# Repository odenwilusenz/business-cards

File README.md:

# business-cards
Business cards for various occasions, that light up.

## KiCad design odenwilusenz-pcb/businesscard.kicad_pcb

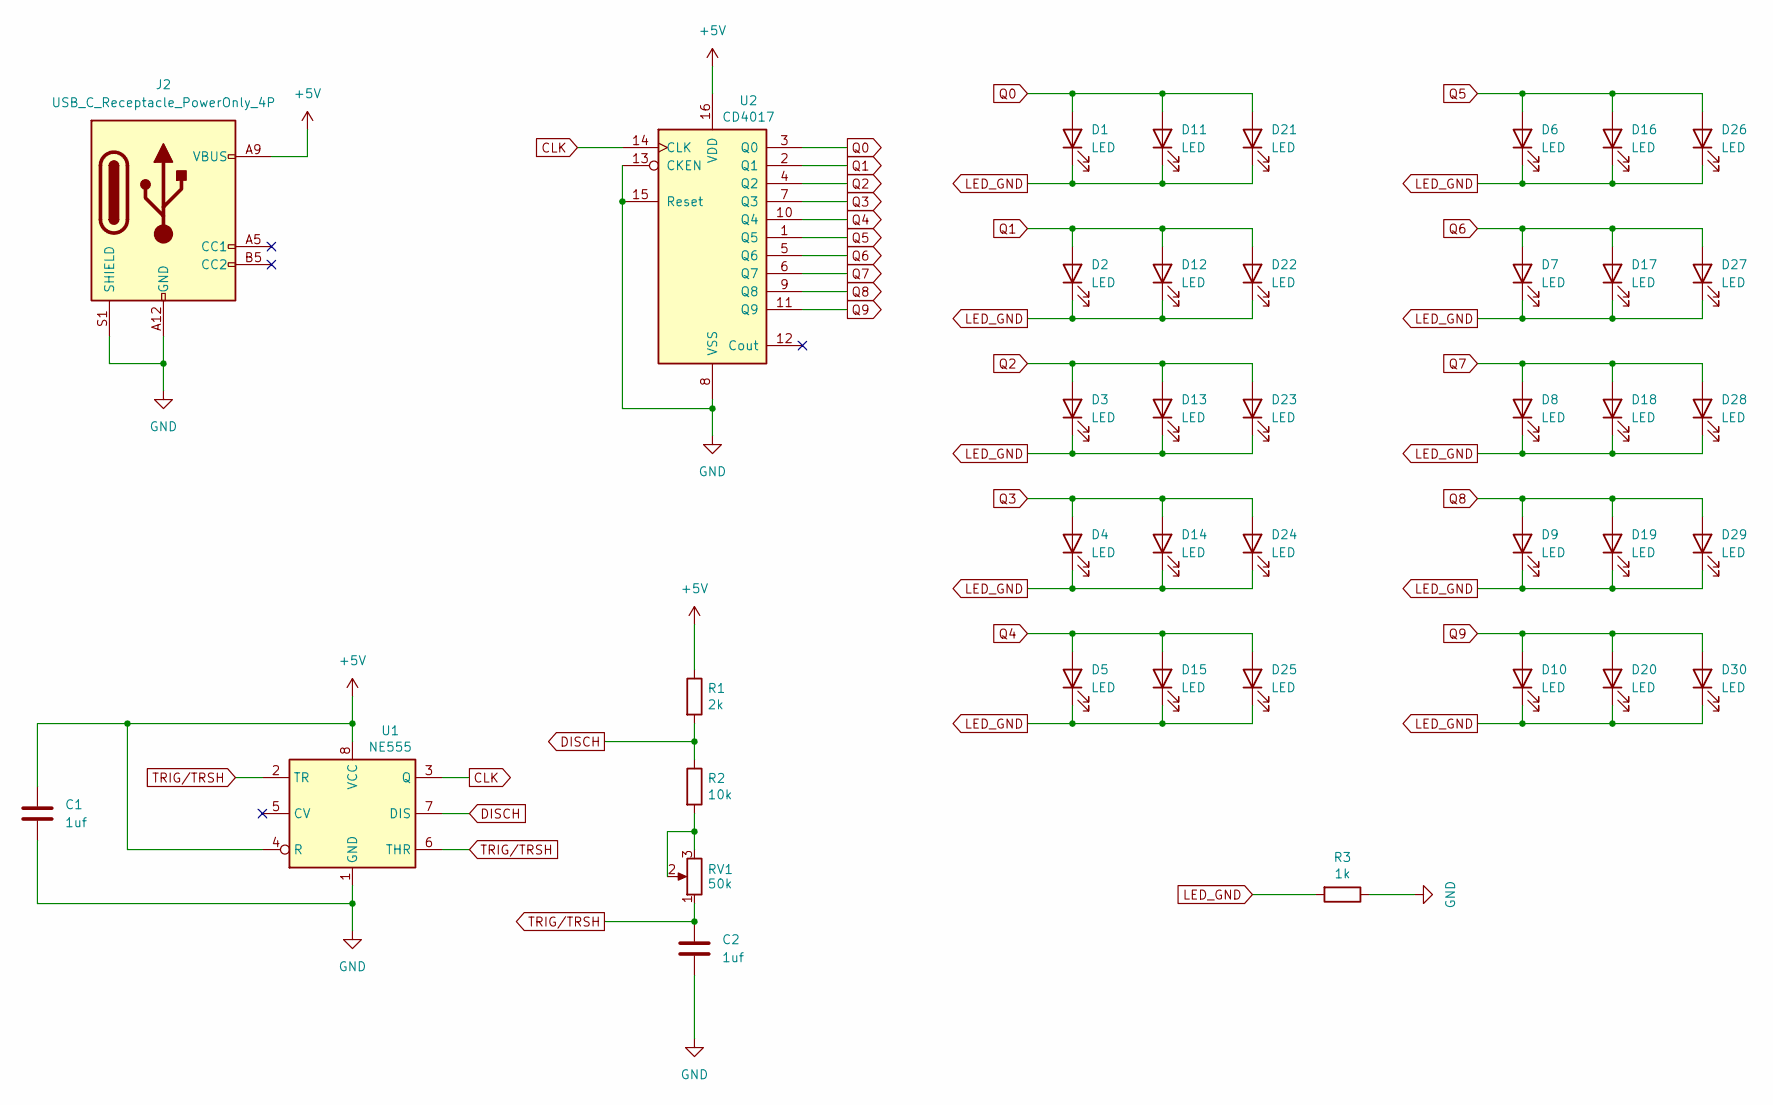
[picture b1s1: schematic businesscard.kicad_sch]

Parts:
C1, C2: 1uf; C_1206_3216Metric_Pad1.33x1.80mm_HandSolder
D1, D2, D3, D4, D5, D6, D7, D8, D9, D10, D11, D12, D13, D14, D15, D16, D17, D18, D19, D20, D21, D22, D23, D24, D25, D26, D27, D28, D29, D30: LED; LED_0805_2012Metric_Pad1.15x1.40mm_HandSolder
J2: USB_C_Receptacle_PowerOnly_4P; usb-c-4-pins
R1: 2k; R_1206_3216Metric_Pad1.30x1.75mm_HandSolder
R2: 10k; R_1206_3216Metric_Pad1.30x1.75mm_HandSolder
R3: 1k; R_1206_3216Metric_Pad1.30x1.75mm_HandSolder
RV1: 50k; Potentiometer_Vishay_TS53YL_Vertical; MPN 3x3 SMD Potentiometer
U1: NE555; SOP-8_3.76x4.96mm_P1.27mm; MPN NE555DR
U2: CD4017; SOIC-16_3.9x9.9mm_P1.27mm

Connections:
+5V: C1.1, J2.A9 (VBUS), J2.B9 (VBUS), R1.1, U1.4 (R), U1.8 (VCC), U2.16 (VDD)
CLK: U1.3 (Q), U2.14 (CLK)
DISCH: R1.2, R2.1, U1.7 (DIS)
GND: C1.2, C2.2, J2.A12 (GND), J2.B12 (GND), J2.S1 (SHIELD), R3.1, U1.1 (GND), U2.8 (VSS), U2.13 (CKEN), U2.15 (Reset)
LED_GND: D1.1 (K), D2.1 (K), D3.1 (K), D4.1 (K), D5.1 (K), D6.1 (K), D7.1 (K), D8.1 (K), D9.1 (K), D10.1 (K), D11.1 (K), D12.1 (K), D13.1 (K), D14.1 (K), D15.1 (K), D16.1 (K), D17.1 (K), D18.1 (K), D19.1 (K), D20.1 (K), D21.1 (K), D22.1 (K), D23.1 (K), D24.1 (K), D25.1 (K), D26.1 (K), D27.1 (K), D28.1 (K), D29.1 (K), D30.1 (K), R3.2
unnamed: R2.2, RV1.2, RV1.3
Q0: D1.2 (A), D11.2 (A), D21.2 (A), U2.3 (Q0)
Q1: D2.2 (A), D12.2 (A), D22.2 (A), U2.2 (Q1)
Q2: D3.2 (A), D13.2 (A), D23.2 (A), U2.4 (Q2)
Q3: D4.2 (A), D14.2 (A), D24.2 (A), U2.7 (Q3)
Q4: D5.2 (A), D15.2 (A), D25.2 (A), U2.10 (Q4)
Q5: D6.2 (A), D16.2 (A), D26.2 (A), U2.1 (Q5)
Q6: D7.2 (A), D17.2 (A), D27.2 (A), U2.5 (Q6)
Q7: D8.2 (A), D18.2 (A), D28.2 (A), U2.6 (Q7)
Q8: D9.2 (A), D19.2 (A), D29.2 (A), U2.9 (Q8)
Q9: D10.2 (A), D20.2 (A), D30.2 (A), U2.11 (Q9)
TRIG/TRSH: C2.1, RV1.1, U1.2 (TR), U1.6 (THR)

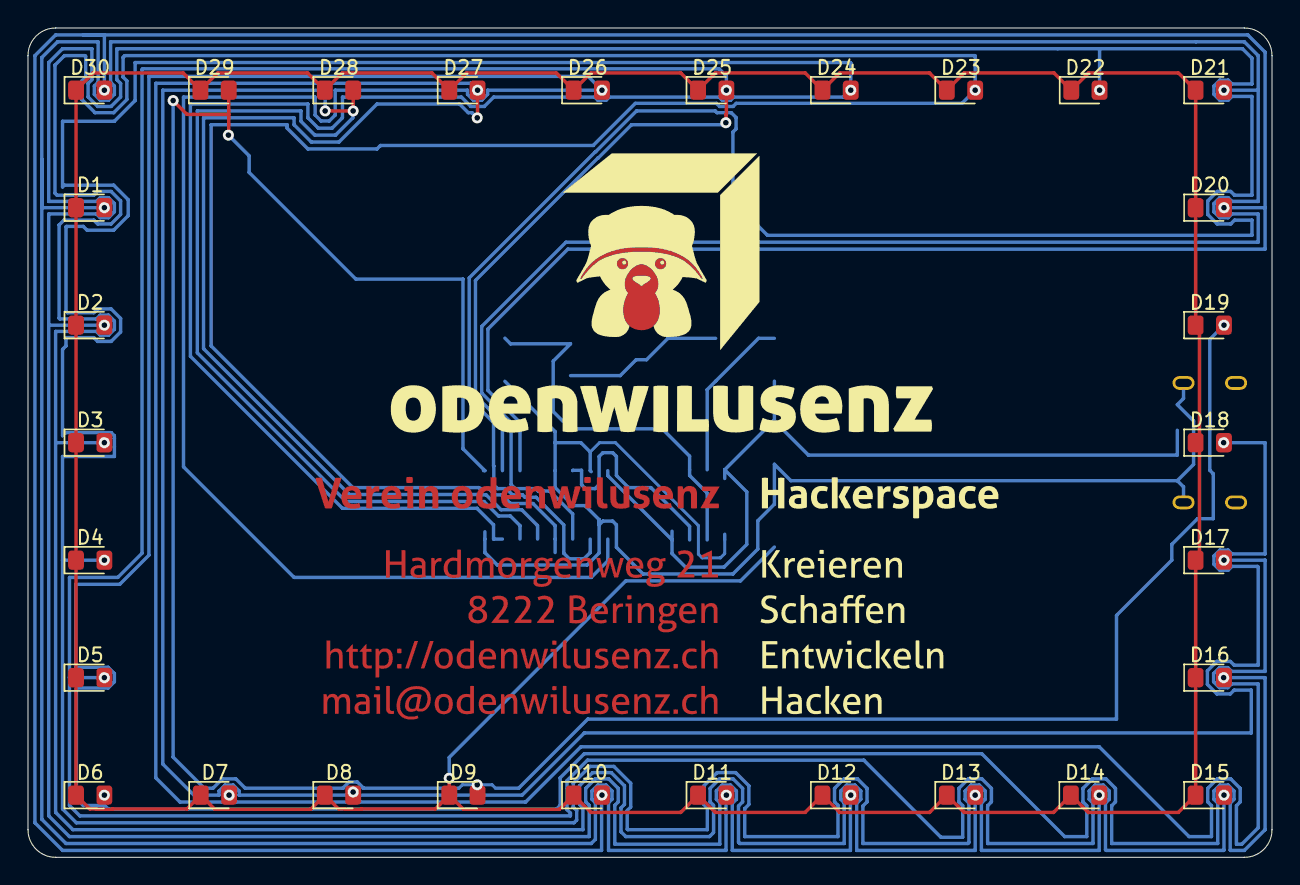
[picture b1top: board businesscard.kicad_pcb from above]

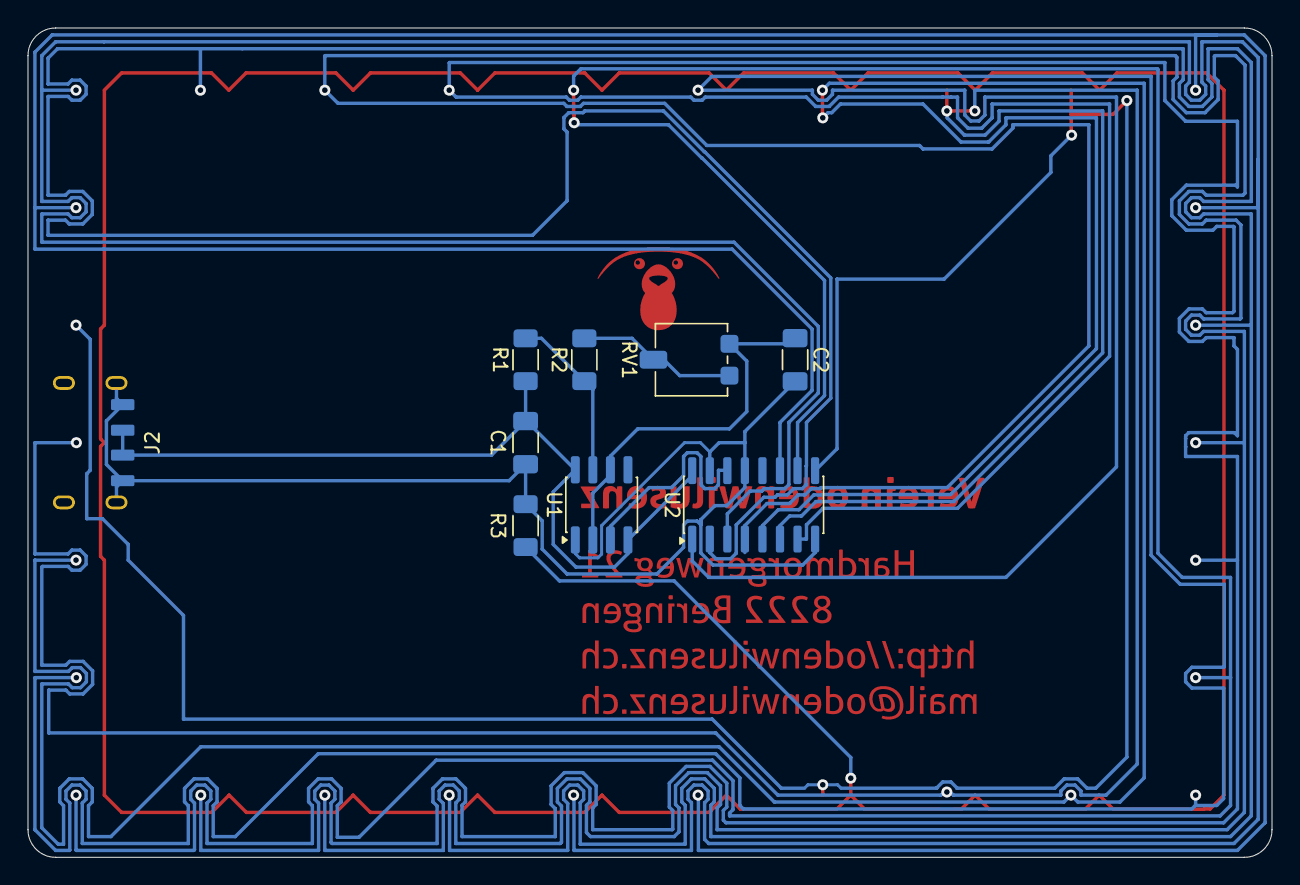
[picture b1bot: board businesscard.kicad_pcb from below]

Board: 2 copper layers, 90.0 x 60.0 mm, 39 parts (9 on the bottom side), 17 nets.

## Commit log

2026-02-11 creating schematic of template pcb
2026-02-11 layouting and routing of leds
2026-02-16 finishing routing and erc
2026-02-16 creating copy for odenwilusenz

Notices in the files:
odenwilusenz-pcb/businesscard.kicad_pcb:
License: CERN-OHL-P
